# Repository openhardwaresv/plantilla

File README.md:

Plantilla para proyectos Open Hardware
=======================================================

Este repositorio tiene el objetivo de servir de plantilla
para facilitar la documentación de proyectos Open-Hardware.

Las carpetas propuestas en esta estructura están basados
en las recomendaciones de buenas prácticas de la OSHWA
traducidas al español que se encuentran disponibles en
http://www.openhardware.sv/acerca-de/buenas-practicas-para-el-hardware-de-fuente-abierta/

Puedes modificar este documento como mejor se ajuste a tus
necesidades sobreescribiendo los textos en cada párrafo y
agregando la información y archivos que consideres conveniente.

Inicia borrando esta sección incluyendo esta línea.

Nombre de tu proyecto
=====================

Escribe aquí una descripción breve de dos o tres párrafos
en donde expliques: ¿Qué es tu proyecto? ¿Para qué sirve? y ¿Cómo
hacerlo funcionar?

Procura no utilizar técnicismos o lenguaje complicado, recuerda
que las personas que leerán esta descripción puede que no tengan
tu mismo nivel de conocimiento o tu misma área de experiencia.

Explica brévemente el funcionamiento esperado de tu proyecto, no es
necesario que escribas todo en detalle, si el funcionamiento requiere
una explicación más detallada puedes hacer referencia a un sitio web
o a otro archivo de texto dentro de la carpeta "docs".

Es muy útil que indiques el nivel de desarrollo de este proyecto sea
"estable", "beta", "incompleto" o "a-penas-funciona".

También puedes agregar en esta sección los créditos correspondientes
si tu proyecto se deriva de otro, nombres o pseudónimos de las
personas que colaboraron, licencia y fecha de última actualización.

Últimas adiciones
=================

Coloca en esta sección los últimos cambios relevantes o correcciones
que hayas realizado a tu proyecto. Es importante que notifiques sobre
cambios que modifiquen el comportamiento de tu proyecto o las salidas
que este genera.

Ejemplo de cambios en la última versión 0.1alpha:

* Agregados textos de ejemplo
* Agregado números de versión

Correcciones:

* Corregidos errores de ortografía

No es necesario que coloques todo el historial de cambios, en vez de eso
puedes crear un archivo en esta carpeta llamado "changelog.txt" con el histórico
completo (preferiblemente en orden cronológico inverso):

> Puede revisar el historial de cambios completo en el archivo changelog.txt

Costo/Lista de Materiales
=========================

Si la lista de materiales de este proyecto es corta puedes incluírla aquí, en
caso contrario puedes crear un archivo llamado "bom.csv" o un archivo de hoja de
cálculo donde puedes detallar la lista de materiales y costos. Procura utilizar
formatos abiertos en la medida de lo posible, por ejemplo eligiendo ODS sobre
Excel.

Pre-requisitos/Requerimientos
=============================

Dedica esta sección a explicar en detalle ¿Qué se requiere para hacer funcionar
tu proyecto?. Debes colocar los requerimientos o pre-requisitos del software
para hacerlo funcionar y herramientas para construirlo.

Para el hardware puedes especificar herramientas o maquinaria específica que se
necesite para construir el proyecto.

Ejemplo:

Requerimientos de software:

* IDE Arduino.

Herramientas requeridas:

* Pinza cortadora de cable.

Construcción y uso
==================

Si el procedimiento de construcción es sencillo, puedes detallarlo en esta
sección, en caso contrario puedes crear un archivo "build.txt" donde detalles el
procedimiento a seguir.

De igual manera si el procedimiento de utilización del software asociado a tu
proyecto es sencillo puedes explicarlo aquí. En caso de que las instrucciones
sean muy extensas, puedes crear un archivo "usage.txt" y hacer referencia
al mismo en esta sección.

Carpetas
========
La estructura de carpetas es muy importante en un proyecto, te permitirá tener
tus proyectos organizados y permitirá a otros compartir fácilmente cambios o 
mejoras. Esta estructura no está escrita en piedra y puedes modificarla según
se adopte mejor a tus necesidades.

Recuerda que dentro de cada carpeta es muy recomendable que incluyas un archivo
llamado "readme.txt" donde detalles los contenidos de la misma.

En la estruuctura de directorios se recomienda incluir por al menos las
siguientes carpetas:

* *doc*: Utiliza esta carpeta para ingresar toda la documentación que consideres
necesaria para tu proyecto. De preferencia utiliza formatos libres como "ODF"
o simples archivos de texto, si puedes crear una página web en HTML recuerda
renombrar el archivo principal como "index.html" para que pueda ser accedido
fácilmente en caso de que alguien copie esta carpeta en un servidor web.
* *src*: Coloca en esta carpeta todos los archivos de código fuente del software
de control de tu proyecto Open Hardware. Si utilizas un IDE como Eclipse o Arduino
copia dentro de src la carpeta del proyecto.
* *dsn* / *diseño*: En esta carpeta coloca todos los archivos para el diseño de tu
proyecto.
  +  *main*: Coloca en esta carpeta los archivos de diseño original que pueden
incluir, pero no limitarse a: Dibujos 2D, diseños 3D, archivos CAD, bibliotecas
de componentes, dibujos técnicos adicionales.
  +  *aux*: Coloca en esta carpeta los archivos de diseño auxiliares que ayuden
a construir tu proyecto. Los archivos de diseño secundario pueden incluír diseños
2D o 3D en formato de intercambio, dibujos técnicos adicionales, formatos listos
para manufactura, artes gráficos adicionales.
* *extra*: Esta carpeta es libre, aquí puedes colocar otros archivos que se
puedan requerir para hacer funcionar o construir tu proyecto. Un ejemplo de ello
puede ser un driver controlador de un dispositivo específico o vínculos a software
relevante, fotografías o videos.

Excepción de responsabilidades
==============================

Es recomendable que incluyas un texto como el siguiente en tus proyectos:

> El presente proyecto se comparte "tal cual" con el único objetivo de que sea útil.
El/los creadores del presente hardware y su software asociado no pueden garantizar su
correcto funcionamiento bajo ninguna circunstancia. El/Los autor/es de este proyecto
no podrá/n hacerse responsable/s de cualquier pérdida de carácter material, personal o
económico a su persona o terceros derivados de la utilización del mismo. Este proyecto
no deberá ser utilizado bajo ninguna circustancia en sistemas de carácter crítico
o sistemas de los cuales dependan vidas de personas de manera directa o indirecta.

Licenciamiento
==============

Agrega aquí la licencia que utilizas en el código fuente de tu proyecto, adicionalmente
agradeceríamos si colocas la nota de atribución de la plantilla al final.

> La plantilla de este README.md ha sido desarrollada por la comunidad openhardware.sv
con el objetivo de facilitar la documentación de proyectos. Esta plantilla está protegida
bajo la licencia CC BY, puedes modificarla y redistribuirla manteniendo esta nota de
atribución del autor.

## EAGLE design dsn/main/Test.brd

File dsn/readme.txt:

Archivos de diseño
==================

Coloca una pequeña descripción de los archivos que incluyes como
parte del diseño. En la carpeta main puedes colocar los archivos
fuente originales y en "extra" formatos de intercambio como se
muestra en el siguiente ejemplo.

Archivos de diseño principal:

* main\Test.sch : Archivo fuente del diagráma eléctrico para Eagle.
* main\Test.brd : Archivo fuente de la tableta impresa para Eagle.

Archivos de diseño auxiliar:
* main\Test.pdf : PDF para impresión del diagrama eléctrico

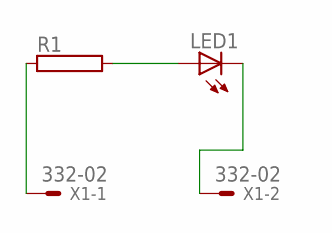
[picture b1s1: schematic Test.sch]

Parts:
LED1: LED_ELD260; LED_LD260
R1: RAC01; AC01
X1: 332-02

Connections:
unnamed: LED1.A, R1.2
unnamed: R1.1, X1.1
unnamed: LED1.K (C), X1.2

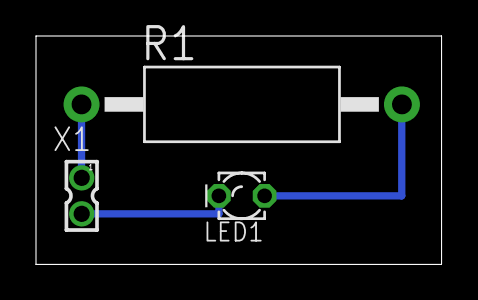
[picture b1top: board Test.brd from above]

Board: 2 copper layers, 22.5 x 12.7 mm, 3 parts (0 on the bottom side), 3 nets.

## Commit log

2013-10-02 Update README.md
    Primera revisión del Leeme.
2013-10-03 Update README.md
    Plantilla actualizada con varias secciones útiles.
2013-10-03 Update README.md
    Correciones ortográficas
2013-10-03 Agregados READMEs y archivos de ejemplo para la plantilla.
2013-10-03 Update README.md
    Movido licenciamiento al final del README. Agregada instrucción de borrado del primero.
2013-10-03 Actualizado el formato del readme.
2013-10-06 Ayudando a Mario con su problema con windos Renombrando la carpeta por problemas con nombres reservador in windos
2013-12-15 Fix file
    Había una etiqueta h1 en lugar de title en el <head>.
